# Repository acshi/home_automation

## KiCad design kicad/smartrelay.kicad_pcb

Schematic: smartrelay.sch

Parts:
BT1: Battery_Cell; PinHeader_1x02_P2.54mm_Vertical
C1, C4, C5, C9: 100nF; C_0603_1608Metric_Pad1.05x0.95mm_HandSolder
C2: 4.7uF; C_0805_2012Metric_Pad1.15x1.40mm_HandSolder
C3: 0.15nF; C_0603_1608Metric_Pad1.05x0.95mm_HandSolder
C6, C7, C10, C11: 10uF; C_0805_2012Metric_Pad1.15x1.40mm_HandSolder
C8: 2200uF; CP_Radial_D10.0mm_P5.00mm; Voltage 10V
D1: D_Photo; PinHeader_1x02_P2.54mm_Vertical
D2: IR1503; PinHeader_1x02_P2.54mm_Vertical
J1: OSTYK42103030; CONN_BARRIER_STRIP_3CIRC_0.325in
J2: AVR-ISP-6; PinHeader_2x03_P2.54mm_Vertical
L1: 4.7uH; L_Radial_D9.5mm_P5.00mm_Fastron_07HVP
Q1, Q2, Q3, Q4, Q5, Q6, Q8: 2N7002WT1G; SOT-323_SC-70_Handsoldering
Q7, Q9: MMBT3904; SOT-23_Handsoldering
R1: 10k; R_0603_1608Metric_Pad1.05x0.95mm_HandSolder
R2, R9: 1M; R_0603_1608Metric_Pad1.05x0.95mm_HandSolder
R3, R4, R5, R6: 22M; R_0603_1608Metric_Pad1.05x0.95mm_HandSolder
R7: 470k; R_0603_1608Metric_Pad1.05x0.95mm_HandSolder
R8: 3.09M; R_0603_1608Metric_Pad1.05x0.95mm_HandSolder
R10: 47R; R_0603_1608Metric_Pad1.05x0.95mm_HandSolder
R12: 680k; R_0603_1608Metric_Pad1.05x0.95mm_HandSolder
R13: 3.9R; R_0603_1608Metric_Pad1.05x0.95mm_HandSolder
R14: 4.7k; R_0603_1608Metric_Pad1.05x0.95mm_HandSolder
R15: 1k; R_0603_1608Metric_Pad1.05x0.95mm_HandSolder
R16: 100k; R_0603_1608Metric_Pad1.05x0.95mm_HandSolder
RL1, RL2: G5RL-K1A-E; LatchingRelayG5RL-K1A-E
U1: ATMEGA328PB-AU; TQFP-32_7x7mm
U2: MCP16251T-I/CH; SOT-23-6_Handsoldering
U3: MAX918ESA; SOIC-8_3.9x4.9mm_P1.27mm
U4: TSOP38338; PinHeader_1x03_P2.54mm_Vertical

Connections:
+5V: C1.1, C6.1, C7.1, J2.2, R1.1, R8.1, R10.1, R12.1, R13.1, R14.1, U1.4, U1.18, U2.5 (VOUT), U3.7, U4.3 (Vs)
/+1.2V: BT1.1 (+), C2.1, L1.1, U1.23, U2.3 (EN), U2.6 (VIN)
/+5V_RELAY: C8.1, R10.2, RL1.5, RL2.5
/CAP_ENABLE: Q5.1, U1.26
/IR_RECV: U1.30, U4.1 (OUT)
/IR_SEND: Q8.1, U1.31; also elsewhere on the board
/LiveIn: J1.1, RL1.3, RL2.3
/LiveOutA: J1.2, RL1.2
/LiveOutB: J1.3, RL2.2
/MISO: J2.1, U1.16
/MOSI: J2.4, U1.15
/NOISE: C11.2, R16.1, U1.24
/RECV_ENABLE: Q6.1, U1.25
/RELAY_CTRL_A_RESET: Q1.1, U1.8
/RELAY_CTRL_A_SET: Q2.1, U1.7
/RELAY_CTRL_B_RESET: Q3.1, U1.2
/RELAY_CTRL_B_SET: Q4.1, U1.1
/SCK: J2.3, U1.17
/WAKEUP: C5.1, U1.32, U3.6
/~RST: J2.5, R1.2, U1.29
GND: BT1.2 (-), C1.2, C2.2, C4.2, C5.2, C6.2, C7.2, C9.2, C10.2, D1.2, J2.6, Q1.2, Q2.2, Q3.2, Q4.2, Q5.2, Q6.2, Q8.2, R2.2, R6.2, R9.2, R15.2, R16.2, U1.5, U1.21, U2.2 (GND), U3.4
unnamed: C3.1, R3.1, R7.2, U3.3
unnamed: C3.2, D1.1, R2.1
unnamed: C4.1, R7.1, U3.2
unnamed: C8.2, Q5.3
unnamed: C9.1, Q7.1, R12.2
unnamed: C10.1, Q9.1, R15.1
unnamed: C11.1, Q9.3, R14.2
unnamed: D2.1 (K), Q8.3
unnamed: D2.2 (A), R13.2
unnamed: L1.2, U2.1 (SW)
unnamed: Q1.3, RL1.1
unnamed: Q2.3, RL1.4
unnamed: Q3.3, RL2.1
unnamed: Q4.3, RL2.4
unnamed: Q6.3, U4.2 (GND)
unnamed: Q7.2, Q9.2
unnamed: R3.2, R4.1
unnamed: R4.2, R5.1
unnamed: R5.2, R6.1
unnamed: R8.2, R9.1, U2.4 (VFB)

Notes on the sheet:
With 1.2V in we only get about 60mA out max!
150mA at 5V (min 3.5V?) for 15ms for relays to switch so 33R coil resistance
max 110uA leakage, 22uA for low leakage nichicon
350uA quiescent
1.6uA quiescent 4mV hysteresis
5mV max offset voltage 1mV typical
less than 1uA in power down mode
1mA 5V draw will maybe take 8mA 1.2V draw, and a 2000mAh battery then last 10 days 100uA would be 100 days and 25uA would be a year
AVR internal pullup is 20 to 50k
Quiescent current, 4uA output
Noise generation circuit
We'll have to take around 300ms to charge before we can drive the relay
max 1.6R rdsOn
For 0.5A bursts w/ 2.2V forward voltage
1.4R rdsOn at 0.5A
Ceramic leakage current probably 0.5uA max

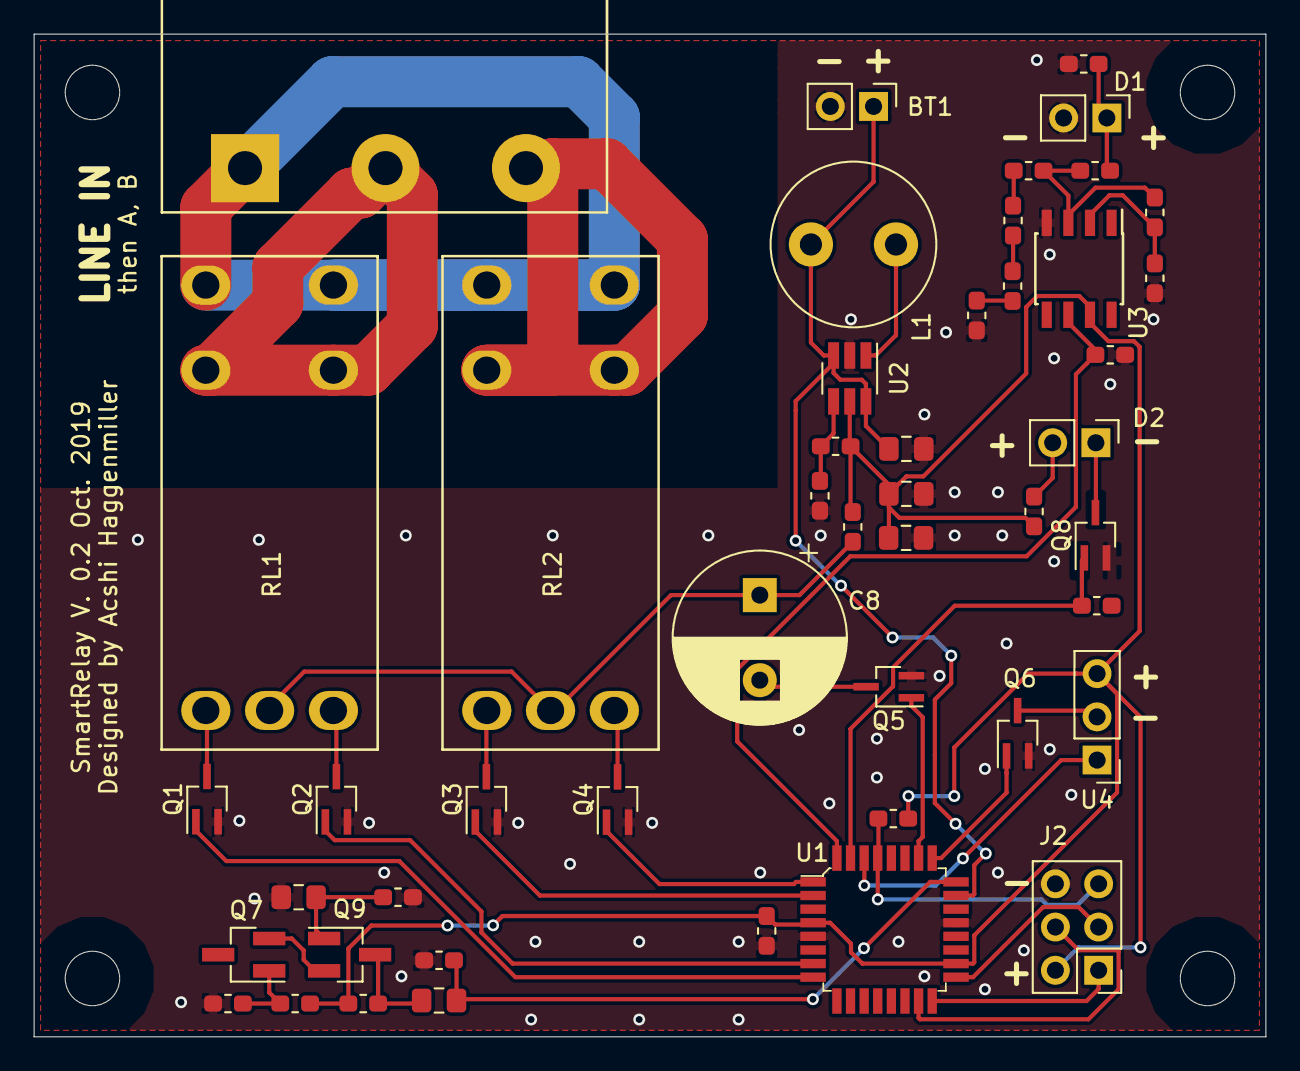
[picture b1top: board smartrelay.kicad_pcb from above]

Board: 2 copper layers, 72.4 x 58.9 mm, 48 parts (0 on the bottom side), 41 nets.

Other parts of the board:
R11: 1k; R_0603_1608Metric_Pad1.05x0.95mm_HandSolder

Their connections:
/IR_SEND: R11.2; also elsewhere on the board

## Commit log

2017-11-22 initial commit of broad home automation project files
2017-11-22 removed non-latching relays and 12V to 5V regulator from schematic
2017-12-26 added circuit board, battery holder, snap fit to scad model
2017-12-26 finished pcb, got it fabricated
2017-12-26 code was able to test turning relay on and off
2017-12-26 added holes for IR components
2018-01-23 firmware works now! and optimized IR protocol performance.
2018-01-23 fixed pcb showing wrong orientation of boost regulator
2018-01-27 sleep mode to save power on battery powered leaf nodes
2018-01-28 implemented deep sleep woken up by level interrupt when receiving IR. extended standby only used while measuring the incoming signal. total ~4ma from battery
2019-10-27 smart relay redesign with smd and without arduino nano
2019-10-27 windows added crlf?
2019-10-27 not sure when I made this change to the scad file
